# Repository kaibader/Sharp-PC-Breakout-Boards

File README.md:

# Sharp-PC-Breakout-Boards
Various Breakout Boards for the Sharp PC-1500/1600 Series

## 40-Pin Cartridge Breakout Boards for the Sharp PC-1500/1600 Series

### v1.0
I've ported the two breakout boards from EagleCAD to KiCad.
The design of two breakout boards was also slightly improved.
There is no functional difference to the older revisions.

### v0.1
Initial release, designed in EagleCAD (which I'm not using anymore).

## Breakout Board for 60 Pin Connector of the Sharp PC-1500/PC-1600 Series
The breakout board was designed to allow easy access to all pins of the Sharp PC connector.

### v1.0
Upated the connector layout: Fixed an issue with a falsely documented FGND pin. Slight improvements in the layout.

### v0.2
Replaced the 1.27 mm pin header: the HIF6A-60PA-1.27DS is compatible with the discontinued JAE PICL-60P-LT (original Sharp-PC connector).
The whole PCB was redesigned: functional units (e.g. data bus, address bus) are now combined.

### v0.1
Initial release, based on a 1.27 mm pin header. Designed in EagleCAD (which I'm not using anymore).

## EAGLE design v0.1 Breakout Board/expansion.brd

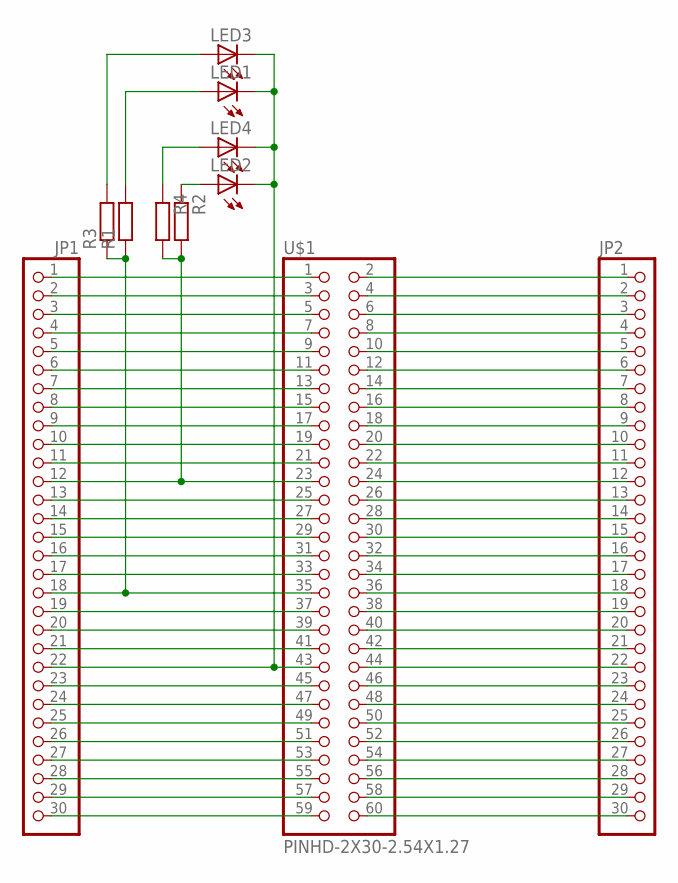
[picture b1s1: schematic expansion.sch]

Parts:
JP1, JP2: PINHD-1X30; 1X30
LED1, LED2, LED3, LED4: LEDCHIP-LED0805; CHIP-LED0805
R1, R2, R3, R4: R-EU_R0805; R0805
U$1: PINHD-2X30-2.54X1.27

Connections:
unnamed: JP1.1, U$1.1
unnamed: JP1.2, U$1.3
unnamed: JP1.3, U$1.5
unnamed: JP1.4, U$1.7
unnamed: JP1.5, U$1.9
unnamed: JP1.6, U$1.11
unnamed: JP1.7, U$1.13
unnamed: JP1.8, U$1.15
unnamed: JP1.9, U$1.17
unnamed: JP1.10, U$1.19
unnamed: JP1.11, U$1.21
unnamed: JP1.12, R2.2, R4.2, U$1.23
unnamed: JP1.13, U$1.25
unnamed: JP1.14, U$1.27
unnamed: JP1.15, U$1.29
unnamed: JP1.16, U$1.31
unnamed: JP1.17, U$1.33
unnamed: JP1.18, R1.1, R3.1, U$1.35
unnamed: JP1.19, U$1.37
unnamed: JP1.20, U$1.39
unnamed: JP1.21, U$1.41
unnamed: JP1.22, LED1.C, LED2.C, LED3.C, LED4.C, U$1.43
unnamed: JP1.23, U$1.45
unnamed: JP1.24, U$1.47
unnamed: JP1.25, U$1.49
unnamed: JP1.26, U$1.51
unnamed: JP1.27, U$1.53
unnamed: JP1.28, U$1.55
unnamed: JP1.29, U$1.57
unnamed: JP1.30, U$1.59
unnamed: JP2.1, U$1.2
unnamed: JP2.2, U$1.4
unnamed: JP2.3, U$1.6
unnamed: JP2.4, U$1.8
unnamed: JP2.5, U$1.10
unnamed: JP2.6, U$1.12
unnamed: JP2.7, U$1.14
unnamed: JP2.8, U$1.16
unnamed: JP2.9, U$1.18
unnamed: JP2.10, U$1.20
unnamed: JP2.11, U$1.22
unnamed: JP2.12, U$1.24
unnamed: JP2.13, U$1.26
unnamed: JP2.14, U$1.28
unnamed: JP2.15, U$1.30
unnamed: JP2.16, U$1.32
unnamed: JP2.17, U$1.34
unnamed: JP2.18, U$1.36
unnamed: JP2.19, U$1.38
unnamed: JP2.20, U$1.40
unnamed: JP2.21, U$1.42
unnamed: JP2.22, U$1.44
unnamed: JP2.23, U$1.46
unnamed: JP2.24, U$1.48
unnamed: JP2.25, U$1.50
unnamed: JP2.26, U$1.52
unnamed: JP2.27, U$1.54
unnamed: JP2.28, U$1.56
unnamed: JP2.29, U$1.58
unnamed: JP2.30, U$1.60
unnamed: LED1.A, R1.2
unnamed: LED2.A, R2.1
unnamed: LED4.A, R4.1
unnamed: LED3.A, R3.2

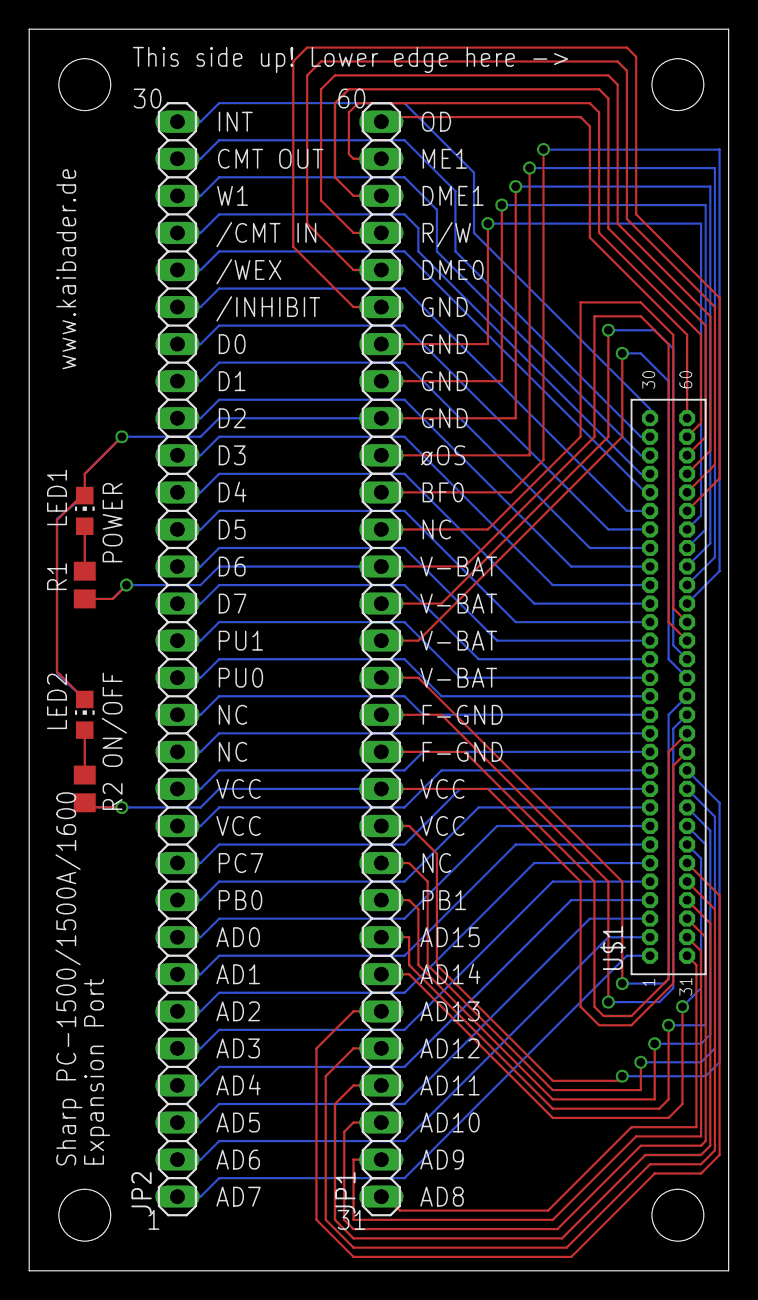
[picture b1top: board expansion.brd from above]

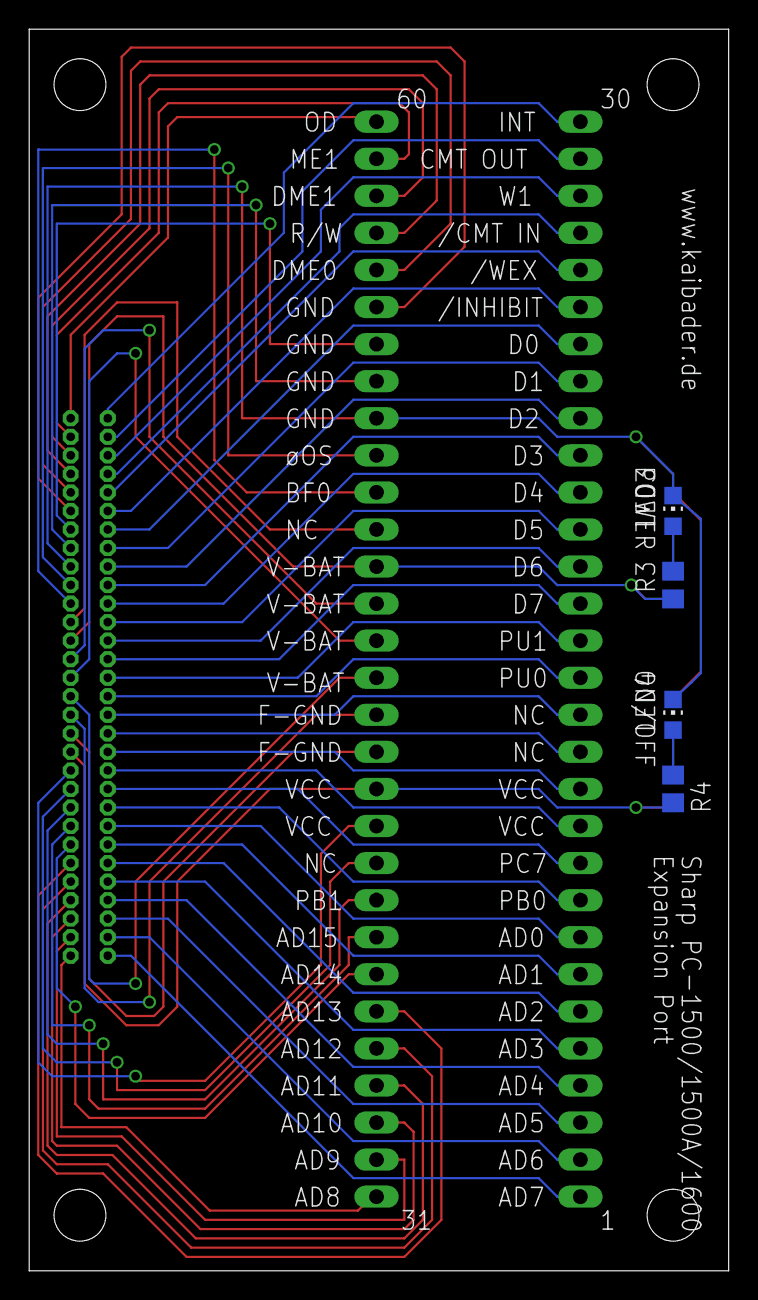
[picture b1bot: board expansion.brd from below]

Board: 2 copper layers, 47.9 x 85.1 mm, 11 parts (4 on the bottom side), 64 nets.

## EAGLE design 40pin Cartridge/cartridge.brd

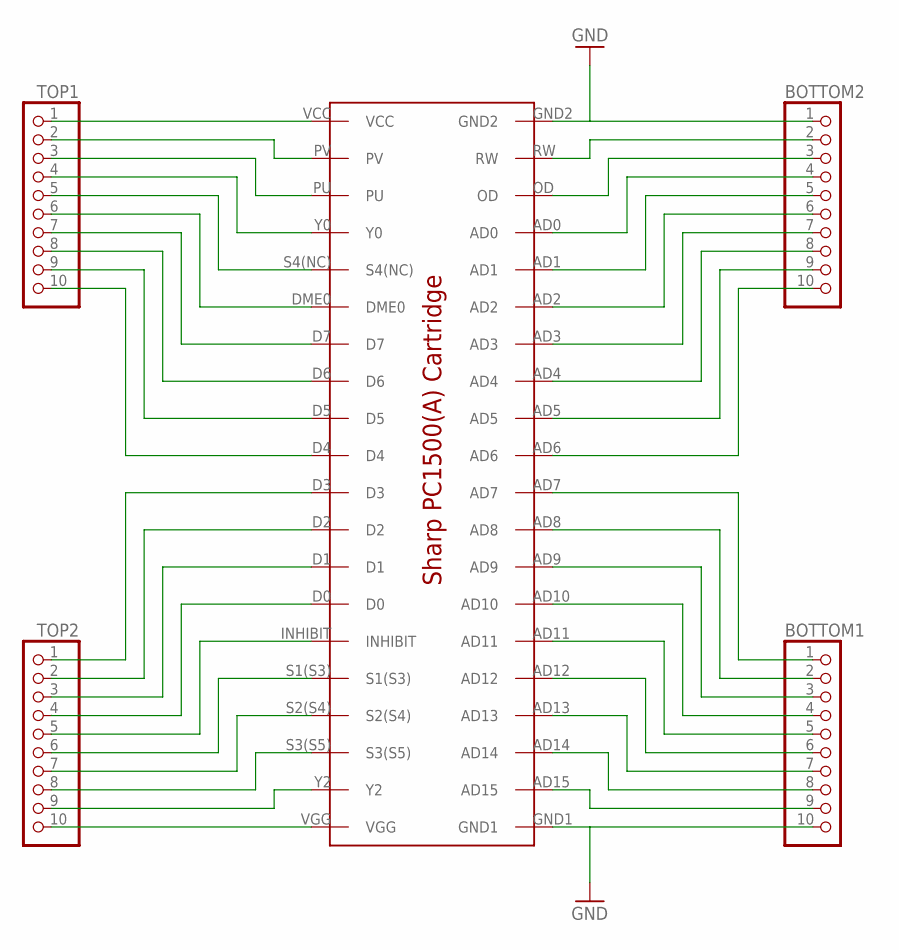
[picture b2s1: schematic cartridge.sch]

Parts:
BOTTOM1, BOTTOM2: PINHD-1X10; 1X10
TOP1, TOP2: PINHD-1X10; 1X10
U$1: SHARP-PC1500-CARTRIDGE

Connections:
AD0: BOTTOM2.4, U$1.AD0
AD1: BOTTOM2.5, U$1.AD1
AD2: BOTTOM2.6, U$1.AD2
AD3: BOTTOM2.7, U$1.AD3
AD4: BOTTOM2.8, U$1.AD4
AD5: BOTTOM2.9, U$1.AD5
AD6: BOTTOM2.10, U$1.AD6
AD7: BOTTOM1.1, U$1.AD7
AD8: BOTTOM1.2, U$1.AD8
AD9: BOTTOM1.3, U$1.AD9
AD10: BOTTOM1.4, U$1.AD10
AD11: BOTTOM1.5, U$1.AD11
AD12: BOTTOM1.6, U$1.AD12
AD13: BOTTOM1.7, U$1.AD13
AD14: BOTTOM1.8, U$1.AD14
AD15: BOTTOM1.9, U$1.AD15
D0: TOP2.4, U$1.D0
D1: TOP2.3, U$1.D1
D2: TOP2.2, U$1.D2
D3: TOP2.1, U$1.D3
D4: TOP1.10, U$1.D4
D5: TOP1.9, U$1.D5
D6: TOP1.8, U$1.D6
D7: TOP1.7, U$1.D7
DME0: TOP1.6, U$1.DME0
GND: BOTTOM1.10, BOTTOM2.1, U$1.GND1, U$1.GND2
INHIBIT: TOP2.5, U$1.INHIBIT
OD: BOTTOM2.3, U$1.OD
PU: TOP1.3, U$1.PU
PV: TOP1.2, U$1.PV
RW: BOTTOM2.2, U$1.RW
S1(S3): TOP2.6, U$1.S1(S3)
S2(S4): TOP2.7, U$1.S2(S4)
S3(S5): TOP2.8, U$1.S3(S5)
S4(NC): TOP1.5, U$1.S4(NC)
VCC: TOP1.1, U$1.VCC
VGG: TOP2.10, U$1.VGG
Y0: TOP1.4, U$1.Y0
Y2: TOP2.9, U$1.Y2

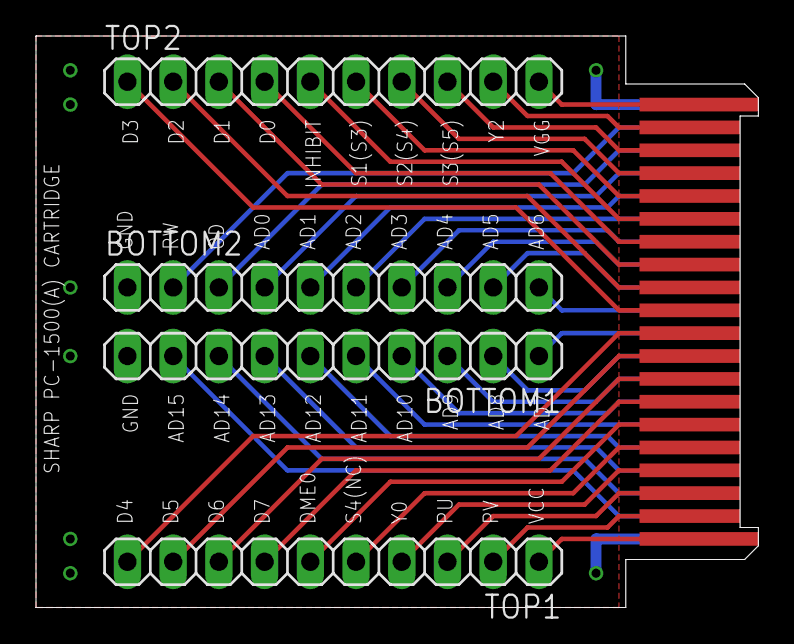
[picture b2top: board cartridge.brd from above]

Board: 2 copper layers, 40.1 x 31.8 mm, 5 parts (0 on the bottom side), 39 nets.

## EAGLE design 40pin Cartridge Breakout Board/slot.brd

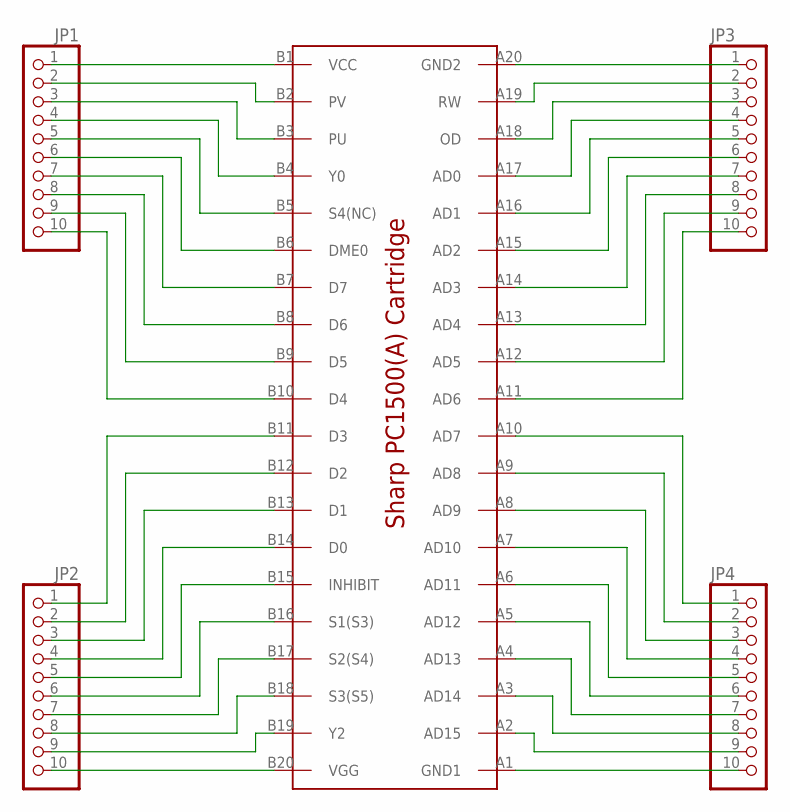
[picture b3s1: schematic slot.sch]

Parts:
JP1, JP2, JP3, JP4: PINHD-1X10; 1X10
U$1: SHARP-PC1500-SLOT

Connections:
unnamed: JP2.10, U$1.B20 (VGG)
unnamed: JP2.9, U$1.B19 (Y2)
unnamed: JP2.8, U$1.B18 (S3(S5))
unnamed: JP2.7, U$1.B17 (S2(S4))
unnamed: JP2.6, U$1.B16 (S1(S3))
unnamed: JP2.5, U$1.B15 (INHIBIT)
unnamed: JP2.4, U$1.B14 (D0)
unnamed: JP2.3, U$1.B13 (D1)
unnamed: JP2.2, U$1.B12 (D2)
unnamed: JP2.1, U$1.B11 (D3)
unnamed: JP1.1, U$1.B1 (VCC)
unnamed: JP1.2, U$1.B2 (PV)
unnamed: JP1.3, U$1.B3 (PU)
unnamed: JP1.4, U$1.B4 (Y0)
unnamed: JP1.5, U$1.B5 (S4(NC))
unnamed: JP1.6, U$1.B6 (DME0)
unnamed: JP1.7, U$1.B7 (D7)
unnamed: JP1.8, U$1.B8 (D6)
unnamed: JP1.9, U$1.B9 (D5)
unnamed: JP1.10, U$1.B10 (D4)
unnamed: JP3.1, U$1.A20 (GND2)
unnamed: JP3.2, U$1.A19 (RW)
unnamed: JP3.3, U$1.A18 (OD)
unnamed: JP3.4, U$1.A17 (AD0)
unnamed: JP3.5, U$1.A16 (AD1)
unnamed: JP3.6, U$1.A15 (AD2)
unnamed: JP3.7, U$1.A14 (AD3)
unnamed: JP3.8, U$1.A13 (AD4)
unnamed: JP3.9, U$1.A12 (AD5)
unnamed: JP3.10, U$1.A11 (AD6)
unnamed: JP4.10, U$1.A1 (GND1)
unnamed: JP4.9, U$1.A2 (AD15)
unnamed: JP4.8, U$1.A3 (AD14)
unnamed: JP4.7, U$1.A4 (AD13)
unnamed: JP4.6, U$1.A5 (AD12)
unnamed: JP4.5, U$1.A6 (AD11)
unnamed: JP4.4, U$1.A7 (AD10)
unnamed: JP4.3, U$1.A8 (AD9)
unnamed: JP4.2, U$1.A9 (AD8)
unnamed: JP4.1, U$1.A10 (AD7)

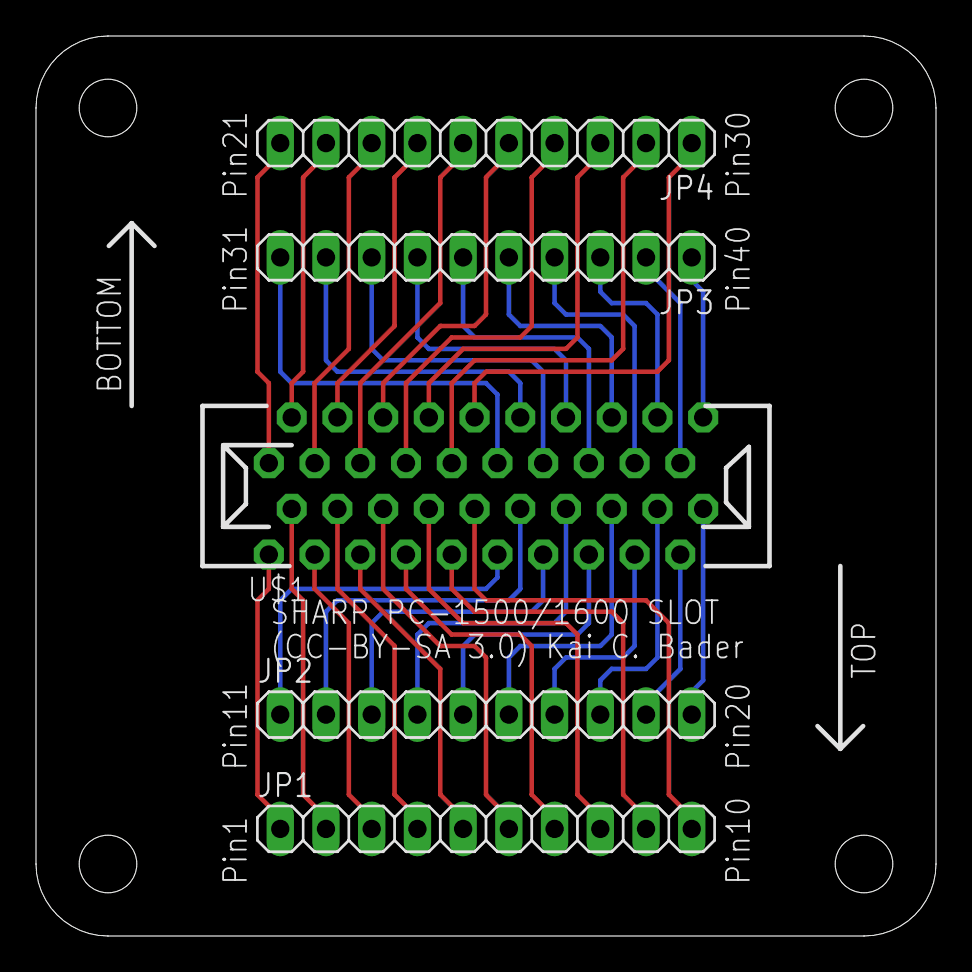
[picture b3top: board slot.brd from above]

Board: 2 copper layers, 50.0 x 50.0 mm, 6 parts (0 on the bottom side), 40 nets.

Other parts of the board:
U$2: DP5050_V1

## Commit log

2016-04-16 Added The Eagle files for the Breakout Boards to a Git repository.
2017-06-07 Updated ignore list
2018-06-13 Housekeeping
    - Moved the v0.1 breakout board to a separate directory.
    - Prepared everything for a new (KiCad) based design.
2018-06-13 Created project files in KiCad
2018-06-20 Created a new version of the 60-pin Breakout Board for the Sharp PC.
2018-06-20 Added a few labels
2018-06-23 Various updates
2018-06-23 Created gerber files of the v0.2 design.
2018-06-23 Some housekeeping
2018-06-23 Updated documentation
2018-06-23 Updated the documentation
2021-05-06 Rev. 1.0 of the Sharp PC-1500 60-Pin Connector Breakout Board.
    Squashed commit of various design updates.
    Fixed one falsely documented FGND pin.
2021-05-08 Updated the two 40-Pin Breakout Boards.
    Ported the boards from EagleCAD to KiCad.
    Slightly improved the board layouts.
    No functional updates.
2021-05-13 Updated the Gerber files.

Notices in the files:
40pin Cartridge Breakout Board/slot.brd:
(CC-BY-SA 3.0) Kai C. Bader
